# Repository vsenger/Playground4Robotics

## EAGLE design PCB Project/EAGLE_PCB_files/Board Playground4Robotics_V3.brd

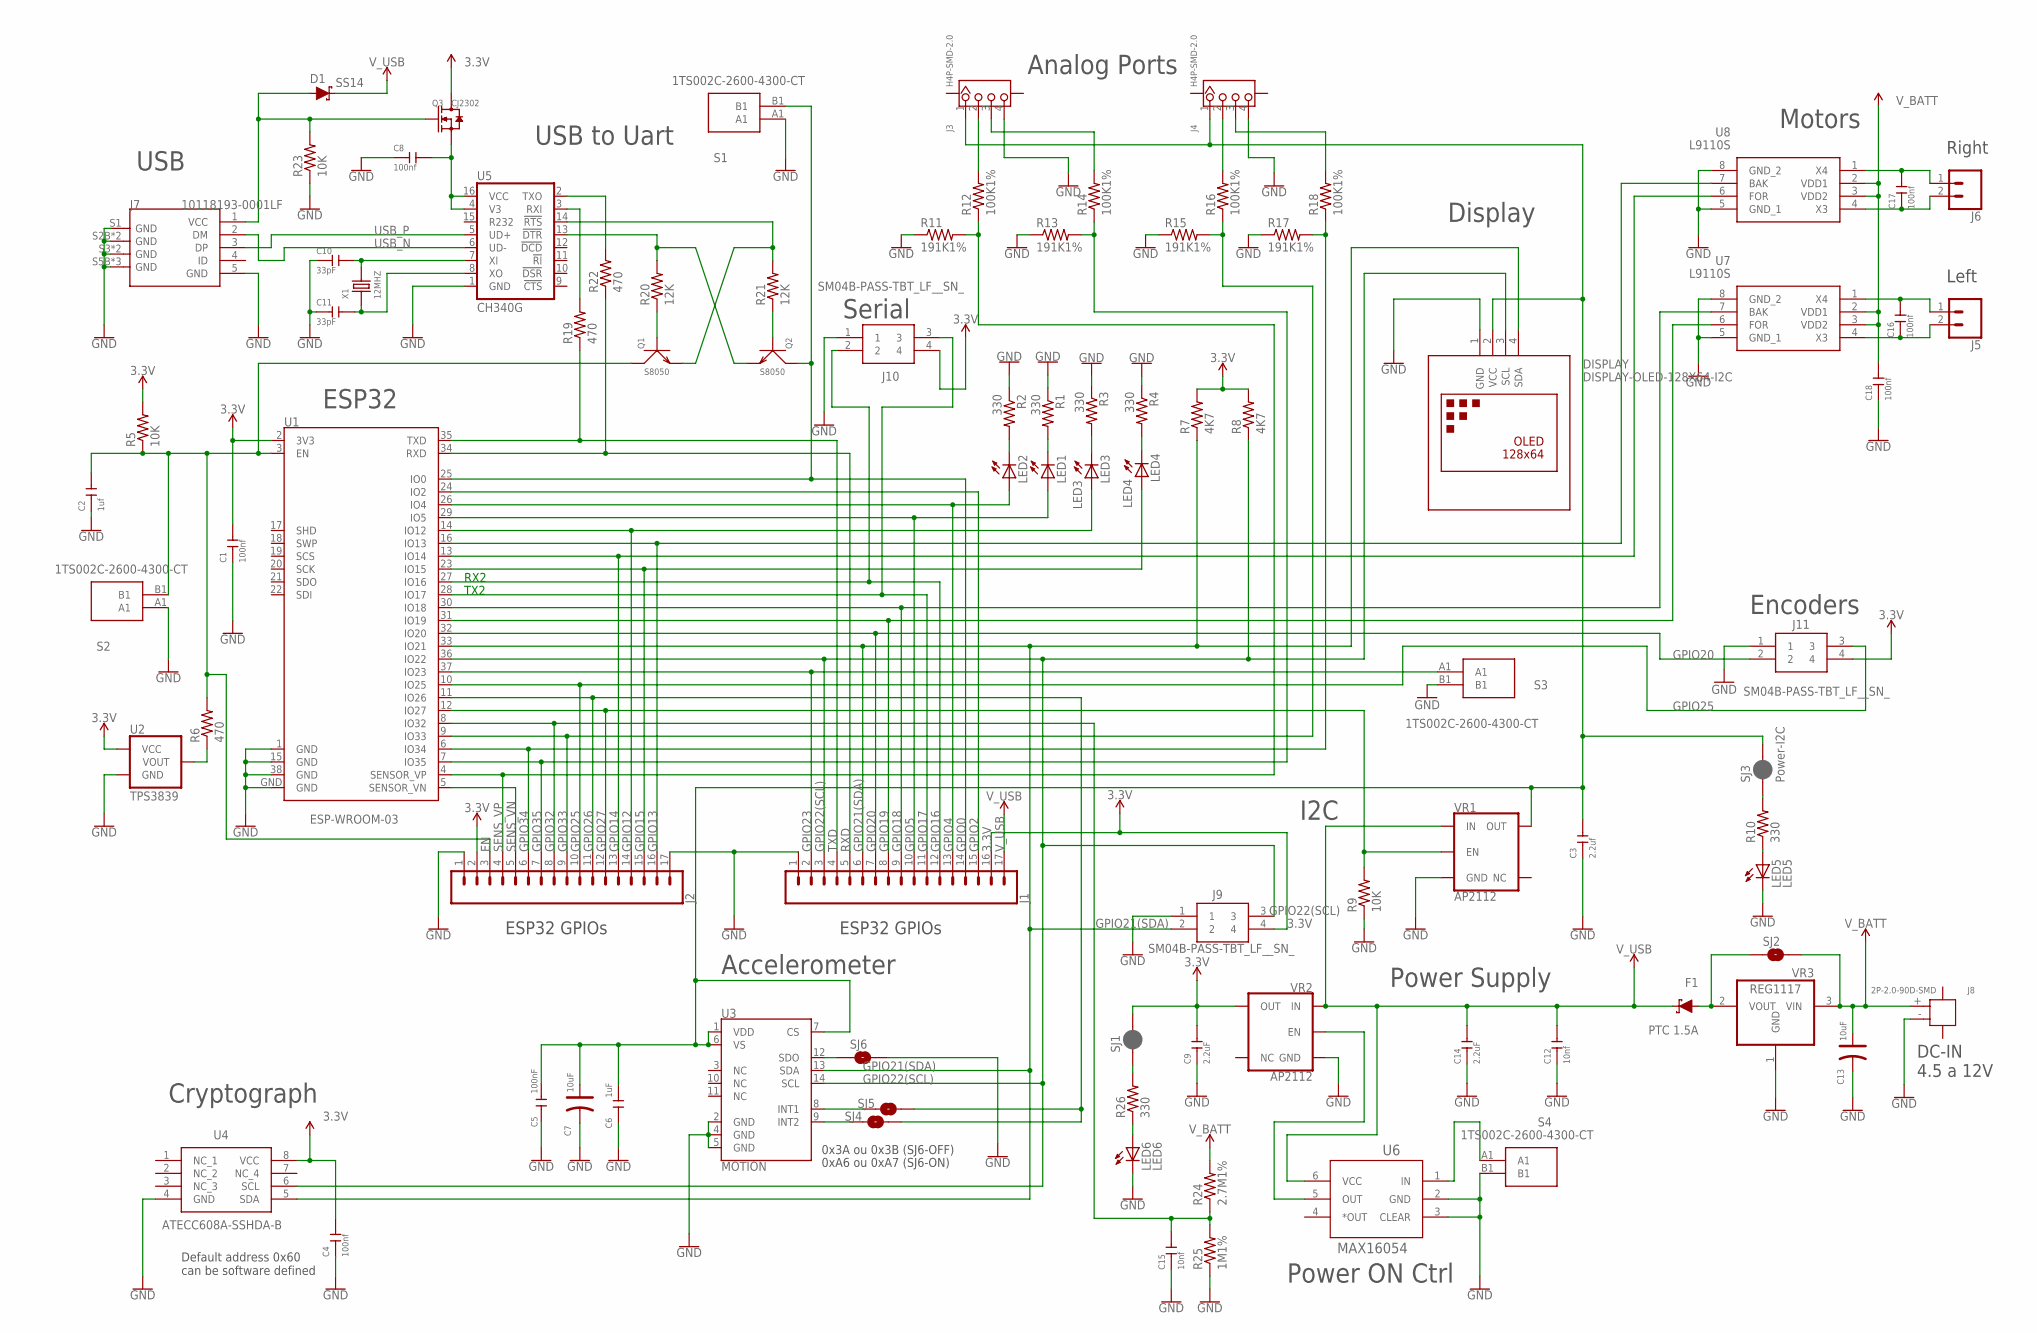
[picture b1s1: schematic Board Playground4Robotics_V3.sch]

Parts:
C1, C4, C8, C16, C17, C18: 100nf; C0603
C2: 1uf; C0603
C3: 2.2uf; C0603
C5: 100nF; C0603
C6: 1uF; C0805
C7, C13: 10uF; AVX-A
C9, C14: 2.2uF; C0603
C10, C11: 33pF; C0603
C12, C15: 10nf; C0603
D1: SS14; SMA-DIODE
DISPLAY: DISPLAY-OLED-128X64-I2C
F1: PTC 1.5A; SMA-DIODE
J1, J2: CONN_17; 1X17
J3, J4: H4P-SMD-2.0; HW4-SMD-2.0
J5, J6: CONN_02POLAR; MOLEX-1X2
J7: 10118193-0001LF; MICRO-USB5+6P-SMD-0.65-B
J8: 2P-2.0-90D-SMD; HW2-SMD-2.0-90D
J9, J10, J11: SM04B-PASS-TBT_LF__SN_; SM04B-PASS-TBT
LED1: LED1; LED-0603
LED2: LED2; LED-0603
LED3: LED3; LED-0603
LED4: LED4; LED-0603
LED5: LED5; LED-0603
LED6: LED6; LED-0603
Q1, Q2: S8050; SOT-23
Q3: CJ2302; SOT-23
R1, R2, R3, R4, R10, R26: 330; 0805
R5, R9, R23: 10K; 0805
R6, R19, R22: 470; 0805
R7, R8: 4K7; 0805
R11, R13, R15, R17: 191K1%; 0805
R12, R14, R16, R18: 100K1%; 0805
R20, R21: 12K; 0805
R24: 2.7M1%; 0805
R25: 1M1%; 0805
S1, S2, S3, S4: 1TS002C-2600-4300-CT; 1TS002C26004300CT
SJ1: Power-Led; SMT-JUMPER_2_NC_PASTE_SILK
SJ2, SJ6: ADXL_ADDRESS; SJ_2S-NO
SJ3: Power-I2C; SMT-JUMPER_2_NC_PASTE_SILK
SJ4, SJ5: INT1; SJ_2S-NO
U1: ESP-WROOM-03
U2: TPS3839; SOT23-3
U3: MOTION; LGA-14
U4: ATECC608A-SSHDA-B; SOIC127P600X175-8N
U5: CH340G; SO016
U6: MAX16054; SOT23-6
U7, U8: L9110S; SOIC127P600X175-8N
VR1, VR2: AP2112; SOT23-5
VR3: REG1117; SOT223
X1: 12MHZ; X2-SMD-5.0X3.2X1.3MM

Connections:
3.3V: C1.2, C4.2, C9.2, J1.16, J2.2, J9.4, J10.4, J11.4, Q3.3 (D), R5.2, R7.2, R8.2, SJ1.2, U1.2 (3V3), U2.3 (VCC), U4.8 (VCC), VR2.5 (OUT)
EN: C2.2, J2.3, Q1.3 (C), R5.1, R6.2, S2.B1, U1.3 (EN)
GND: C1.1, C2.1, C3.1, C4.1, C5.1, C6.2, C7.-, C8.1, C9.1, C10.1, C11.1, C12.1, C13.-, C14.1, C15.1, C18.1, DISPLAY.1 (GND), J1.1, J2.1, J2.17, J3.4, J4.4, J7.5 (GND), J7.S1 (GND), J7.S2B (GND), J7.S2T (GND), J7.S3 (GND), J7.S4 (GND), J7.S5B (GND), J7.S5T (GND), J7.S6 (GND), J8.- (2), J9.1, J10.1, J11.1, LED5.C, LED6.C, R1.1, R2.1, R3.1, R4.1, R9.1, R11.1, R13.1, R15.1, R17.1, R23.1, R25.1, S1.A1, S2.A1, S3.B1, S4.B1, SJ6.2, U1.1 (GND), U1.15 (GND), U1.38 (GND), U1.GND, U2.1 (GND), U3.2 (GND), U3.4 (GND), U3.5 (GND), U4.4 (GND), U5.1 (GND), U6.2 (GND), U6.3 (CLEAR), U7.5 (GND_1), U7.8 (GND_2), U8.5 (GND_1), U8.8 (GND_2), VR1.2 (GND), VR2.2 (GND), VR3.1 (GND)
GPIO0: J1.14, Q2.3 (C), S1.B1, U1.25 (IO0)
GPIO2: J1.15, U1.24 (IO2)
GPIO4: J1.13, LED2.A, U1.26 (IO4)
GPIO5: J1.10, LED1.A, U1.29 (IO5)
GPIO12: J2.14, LED3.A, U1.14 (IO12)
GPIO13: J2.16, U1.16 (IO13), U8.7 (BAK)
GPIO14: J2.13, U1.13 (IO14), U8.6 (FOR)
GPIO15: J2.15, LED4.A, U1.23 (IO15)
GPIO16: J1.12, J10.2, U1.27 (IO16)
GPIO17: J1.11, J10.3, U1.28 (IO17)
GPIO18: J1.9, U1.30 (IO18), U7.7 (BAK)
GPIO19: J1.8, U1.31 (IO19), U7.6 (FOR)
GPIO20: J1.7, J11.2, U1.32 (IO20)
GPIO21(SDA): DISPLAY.4 (SDA), J1.6, J9.2, R7.1, U1.33 (IO21), U3.13 (SDA), U4.5 (SDA)
GPIO22(SCL): DISPLAY.3 (SCL), J1.3, J9.3, R8.1, U1.36 (IO22), U3.14 (SCL), U4.6 (SCL)
GPIO23: J1.2, S3.A1, U1.37 (IO23)
GPIO25: J2.10, J11.3, U1.10 (IO25)
GPIO26: J2.11, SJ4.2, SJ5.2, U1.11 (IO26)
GPIO27: J2.12, R9.2, U1.12 (IO27), VR1.3 (EN)
GPIO32: C15.2, J2.8, R24.1, R25.2, U1.8 (IO32)
GPIO33: J2.9, R15.2, R16.1, U1.9 (IO33)
GPIO34: J2.6, R17.2, R18.1, U1.6 (IO34)
GPIO35: J2.7, R13.2, R14.1, U1.7 (IO35)
unnamed: D1.A, J7.1 (VCC), Q3.1 (G), R23.2
unnamed: C17.2, J6.1, U8.1 (X4)
unnamed: R6.1, U2.2 (VOUT)
unnamed: J3.2, R12.2
unnamed: SJ5.1, U3.8 (INT1)
unnamed: SJ4.1, U3.9 (INT2)
unnamed: C8.2, Q3.2 (S), U5.4 (V3), U5.16 (VCC)
unnamed: S4.A1, U6.1 (IN)
unnamed: C10.2, U5.7 (XI), X1.2
unnamed: U6.5 (OUT), VR2.3 (EN)
unnamed: Q1.1 (B), R20.1
unnamed: C11.2, U5.8 (XO), X1.1
unnamed: SJ6.1, U3.12 (SDO)
unnamed: C17.1, J6.2, U8.4 (X3)
unnamed: C16.2, J5.1, U7.1 (X4)
unnamed: C16.1, J5.2, U7.4 (X3)
unnamed: J3.3, R14.2
unnamed: Q2.1 (B), R21.1
unnamed: F1.A, SJ2.1, VR3.2 (VOUT)
unnamed: LED2.C, R2.2
unnamed: LED1.C, R1.2
unnamed: Q1.2 (E), R21.2, U5.14 (!RTS)
unnamed: LED4.C, R4.2
unnamed: LED3.C, R3.2
unnamed: Q2.2 (E), R20.2, U5.13 (!DTR)
unnamed: J4.2, R16.2
unnamed: J4.3, R18.2
unnamed: C3.2, C5.2, C6.1, C7.+, DISPLAY.2 (VCC), J3.1, J4.1, SJ3.2, U3.1 (VDD), U3.6 (VS), U3.7 (CS), VR1.5 (OUT)
unnamed: R19.2, U5.3 (RXI)
unnamed: R22.2, U5.2 (TXO)
unnamed: LED6.A, R26.1
unnamed: R26.2, SJ1.1
unnamed: LED5.A, R10.1
unnamed: R10.2, SJ3.1
RXD: J1.5, R22.1, U1.34 (RXD)
SENS_VN: J2.5, U1.5 (SENSOR_VN)
SENS_VP: J2.4, R11.2, R12.1, U1.4 (SENSOR_VP)
TXD: J1.4, R19.1, U1.35 (TXD)
USB_N: J7.2 (DM), U5.6 (UD-)
USB_P: J7.3 (DP), U5.5 (UD+)
V_BATT: C13.+, C18.2, J8.+ (1), R24.2, SJ2.2, U7.2 (VDD1), U7.3 (VDD2), U8.2 (VDD1), U8.3 (VDD2), VR3.3 (VIN)
V_USB: C12.2, C14.2, D1.C, F1.C, J1.17, U6.6 (VCC), VR1.1 (IN), VR2.1 (IN)

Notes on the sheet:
USB
I2C
Accelerometer
Default address 0x60 can be software defined
Serial
ESP32
Power Supply
USB to Uart
Analog Ports
ESP32 GPIOs
RX2
TX2
Display
0x3A ou 0x3B (SJ6-OFF)
0xA6 ou 0xA7 (SJ6-ON)
Power ON Ctrl
Cryptograph
Encoders
Motors
Left
Right
DC-IN 4.5 a 12V

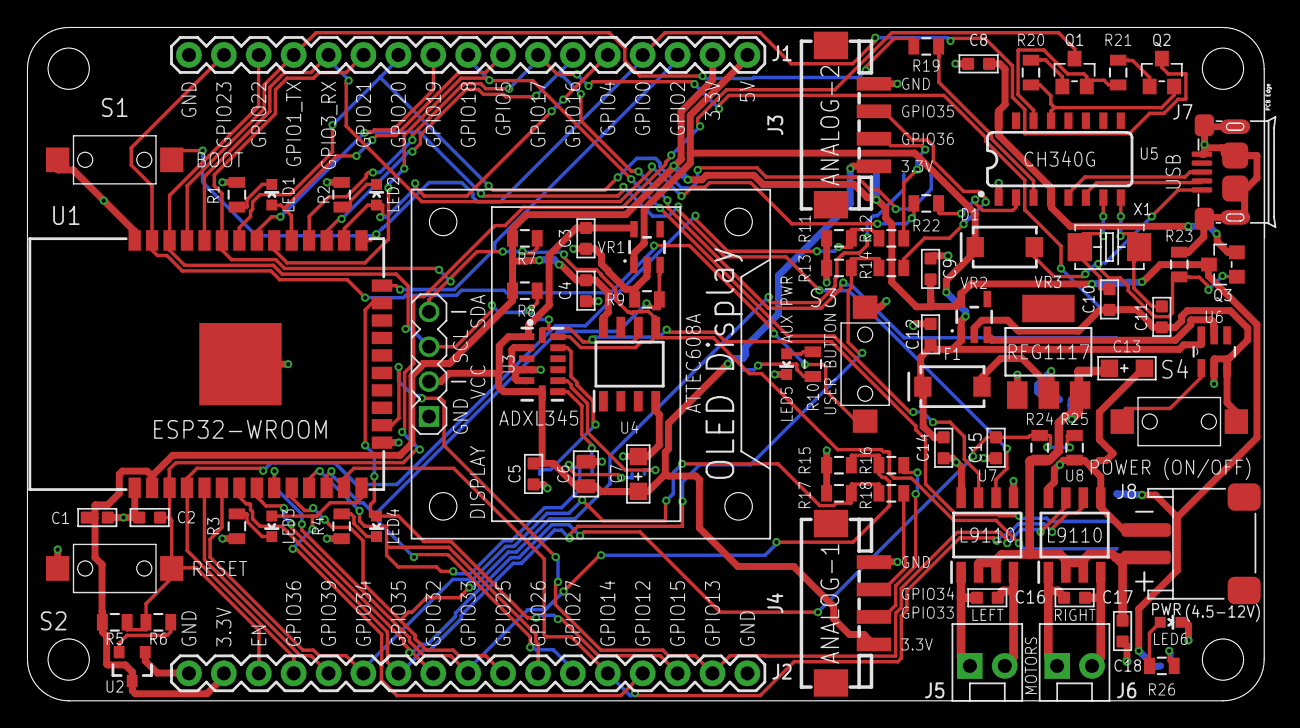
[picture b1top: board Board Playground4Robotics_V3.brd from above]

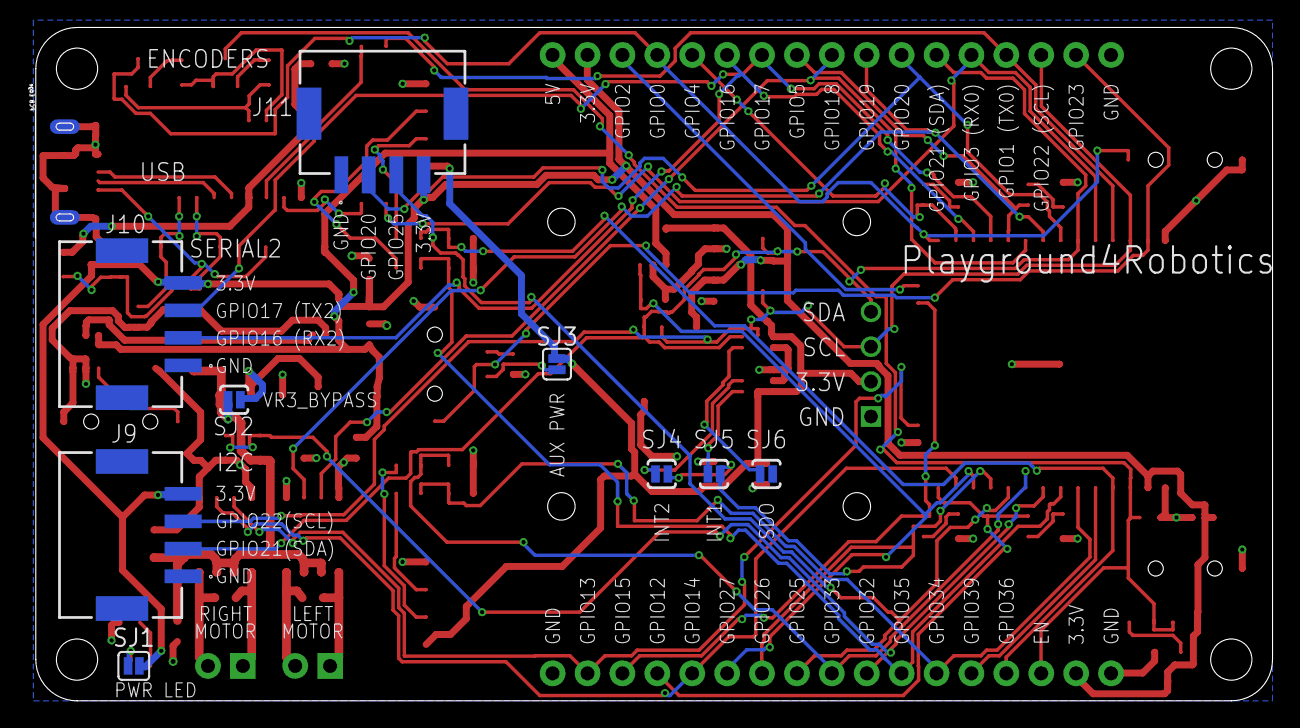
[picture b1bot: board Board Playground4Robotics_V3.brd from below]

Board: 2 copper layers, 90.0 x 49.0 mm, 89 parts (9 on the bottom side), 68 nets.

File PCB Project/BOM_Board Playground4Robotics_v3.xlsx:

Qty | Value | Package | Parts | Description | PART_NUMBER | Unit PRICE (100 PCBs) | SUBTOTAL
6 | 330 | 0805 | R1, R2, R3, R4, R10, R26 | 330 ±1% 1/8W ±100ppm/℃ 0805 Chip Resistor - Surface Mount RoHS | RC0805FR-07330RL | 9.9819999999999996E-3 | 5.9892000000000001E-2
3 | 10K | 0805 | R5, R9, R23 | 10K ±5% 1/8W ±200ppm/℃ 0805 Chip Resistor - Surface Mount RoHS | CR0805J80103G | 2.5929999999999998E-3 | 7.7789999999999995E-3
3 | 470 | 0805 | R6, R19, R22 | 470 ±1% 1/8W ±100ppm/℃ 0805 Chip Resistor - Surface Mount RoHS | RC0805FR-07470RL | 2.8029999999999999E-3 | 8.4089999999999998E-3
2 | 4K7 | 0805 | R7, R8 | 4.7K ±1% 1/8W ±100ppm/℃ 0805 Chip Resistor - Surface Mount RoHS | RCT054K7 FLF | 7.9220000000000002E-3 | 1.5844E-2
4 | 191K1% | 0805 | R11, R13, R15, R17 | 191K ±1% 1/8W ±100ppm/℃ 0805 Chip Resistor - Surface Mount RoHS | AC0805FR-07191KL | 5.4120000000000001E-3 | 2.1648000000000001E-2
4 | 100K1% | 0805 | R12, R16, R14, R18 | 100K ±1% 1/8W ±100ppm/℃ 0805 Chip Resistor - Surface Mount RoHS | RS-05K1003FT | 7.0280000000000004E-3 | 2.8112000000000002E-2
2 | 12K | 0805 | R20, R21 | 12K ±5% 1/8W ±100ppm/℃ 0805 Chip Resistor - Surface Mount RoHS | AC0805FR-0712KL | 1.853E-3 | 3.7060000000000001E-3
1 | 2.7M1% | 0805 | R24 | 2.7M ±1% 1/8W ±100ppm/℃ 0805 Chip Resistor - Surface Mount RoHS | 0805W8F2704T5E | 1.825E-3 | 1.825E-3
1 | 1M1% | 0805 | R25 | 1M ±1% 1/8W ±100ppm/℃ 0805 Chip Resistor - Surface Mount RoHS | RC0805FR-071ML | 4.1520000000000003E-3 | 4.1520000000000003E-3
7 | 100nf | C0603 | C1, C4, C5, C8, C16, C17, C18 | 100nF ±10% 50V X7R 0603 Multilayer Ceramic Capacitors MLCC - SMD/SMT RoHS | C0603B104K500NT | 7.8560000000000001E-3 | 5.4991999999999999E-2
1 | 1uF | C0603 | C2 | 1uF ±10% 16V X7R 0603Multilayer Ceramic Capacitors MLCC - SMD/SMT RoHS | CL10A105KO8NNNC | 6.6E-3 | 6.6E-3
3 | 2.2uf | C0603 | C3, C9, C14 | 2.2uF ±10% 16V X5R 0603 Multilayer Ceramic Capacitors MLCC - SMD/SMT RoHS | 0603X225K160NT | 1.7375999999999999E-2 | 5.2127999999999994E-2
1 | 1uF | C0805 | C6 | 1uF ±10% 16V X7R 0805 Multilayer Ceramic Capacitors MLCC - SMD/SMT RoHS | FS21B105K160ECG | 3.7949999999999998E-2 | 3.7949999999999998E-2
2 | 10uF | AVX-A | C7, C13 | 10uF ±10% 10V 3 Ω @ 100kHz -55℃ ~ +125℃ CASE-A_3216 Tantalum Capacitors RoHS | CA45-A-16V-10uF-K | 6.7254999999999995E-2 | 0.13450999999999999
2 | 33pF | C0603 | C10, C11 | 33pF ±5% 50V C0G 0603 Multilayer Ceramic Capacitors MLCC - SMD/SMT RoHS | 0603N330F500CT | 1.4840000000000001E-2 | 2.9680000000000002E-2
2 | 10nf | C0603 | C12, C15 | 10nF ±5% 50V NP0 0603 Multilayer Ceramic Capacitors MLCC - SMD/SMT RoHS | 0603B103J500CT | 7.1798000000000001E-2 | 0.143596
1 | 12MHZ | X2-SMD-5.0X3.2X1.3MM | X1 | 12MHz ±30ppm 20pF 150Ω SMD-5032_2P SMD Crystal Resonators RoHS | XSHEELNANF-12MHZ | 0.160606 | 0.160606
4 | green | LED-0603 | LED1, LED2, LED3, LED4 | Green 520~535nm 0603 Light Emitting Diodes (LED) RoHS | 19-217/GHC-YR1S2/3T | 3.5455E-2 | 0.14182
1 | yellow | LED-0603 | LED5 | Yellow 585.5~594.5nm 0603 Light Emitting Diodes (LED) RoHS | 19-217/Y5C-AP1Q2/3T | 2.0181000000000001E-3 | 2.0181000000000001E-3
1 | red | LED-0603 | LED6 | Red 617.5~633.5nm 0603 Light Emitting Diodes (LED) RoHS | 19-217/R6C-AL1M2VY/3T | 1.7727E-2 | 1.7727E-2
1 | SS14 | SMA-DIODE | D1 | SMA Schottky Barrier Diodes (SBD) RoHS | SS14 | 9.6050000000000007E-3 | 9.6050000000000007E-3
1 | FUSE PTC 1.5 A | 1206 | D2 / F1 | Polymeric 8V 1.5A 200ms 290mΩ 1206 PTC Resettable | 1206L075THYR | 3.4000000000000002E-2 | 3.4000000000000002E-2
2 | AP2112 | SOT23-5 | VR1, VR2 | AP2112-3.3v Fixed 6V 3.3V 600mA SOT-25 Low Dropout Regulators(LDO) RoHS | AP2112K-3.3TRG1 | 0.124252 | 0.248504
1 | REG1117 5volts | SOT223 | VR3 | 800mA and 1A Low Dropout (LDO) Positive Regulator 5 volts | AMS1117-5.0 | 3.7600000000000001E-2 | 3.7600000000000001E-2
1 | ESP-WROOM-03 | ESP-WROOM-03 | U1 | ESP32 Module WIFI Modules RoHS | ESP32-WROOM-32 | 2.6151520000000001 | 2.6151520000000001
1 | TPS3839 | SOT23-3 | U2 | Simple reset/Power-on reset 1 Push-pull,Totem pole Low effective 2.93V SOT-23(S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 | TPS3839K33DBZR | 0.39696999999999999 | 0.39696999999999999
1 | MOTION | LGA-14 | U3 | Analog Devices ADXL345 3-Axis SPI/I2C 2/4/8/16g Accelerometer | ADXL345BCCZ-RL7 | 1.1636359999999999 | 1.1636359999999999
1 | ATECC608A-SSHDA-B | SOIC127P600X175-8N | U4 | Cryptoathentication ECC608A SOIC | ATECC608A_SSHDA-B | 1.827 | 1.827
1 | CH340G | SO016 | U5 | Transceiver USB 2.0 2Mbps SOP-16_150mil USB ICs RoHS | CH340G | 0.275758 | 0.275758
1 | MAX16054 | SOT23-6 | U6 | TSOT-23-6 Interface - Specialized RoHS | MAX16054AZT+T | 1.204545 | 1.204545
2 | L9110S | SOIC127P600X175-8N | U7, U8 | Motor Drivers SOP-8_150mil RoHS | L9110S | 0.11459999999999999 | 0.22919999999999999
2 | S8050 | SOT-23 | Q1, Q2 | NPN 500mA 25V 300mW SOT-23 Transistors (NPN/PNP) RoHS | S8050 | 7.5909999999999997E-3 | 1.5181999999999999E-2
1 | CJ2302 | SOT-23 | Q3 | N Channel 20V 2.1A 1.2V @ 50uA 60 mΩ @ 3.6A,4.5V 350mW SOT-23(SOT-23-3) MOSFET 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 | CJ2302 S2 | 3.0800000000000001E-2 | 3.0800000000000001E-2
4 | CONN_17 | 1X17 | J1, J2 | 10P 2.54MM Stackable Long Connector Female Pin Header (Arduino style) | SeeedStudio (320030001) |  | 0
2 | H4P-SMD-2.0 | HW4-SMD-2.0 | J3, J4 | PA SMD Wire To Board / Wire To Wire Connector RoHS | BM04B-PASS-TFT(LF)(SN) | 0.32150000000000001 | 0.64300000000000002
2 | KK | MOLEX-1X2 | J5, J6 | Header Male Pin 0.100"(2.54mm) 2 Through Hole,P=2.54mm Wire To Board / Wire To 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 | A2543WV-2P | 2.63E-2 | 5.2600000000000001E-2
1 | 10118193-0001LF | MICRO-USB5+6P-SMD-0.65-B | J7 | MICRO-USB-SMD-B-(10118193-0001LF) | (10118193-0001LF) ou (U254-051T-4BH83-F1S) | 0.14419999999999999 | 0.14419999999999999
1 | 2P-2.0-90D-SMD | HW2-SMD-2.0-90D | J8 | CONN-HEADER-SMD-PH-SIDE-(2P-2.0MM) | S2B-PH-SM4-TB(LF)(SN) | 0.12670000000000001 | 0.12670000000000001
3 | SM04B-PASS-TBT_LF__SN_ | SM04B-PASS-TBT | J9, J10, J11 | PA Header Male Pin 0.079"(2.00mm) 4 Through Hole,P=2mm Wire To Board / Wire To 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 | SM04B-PASS-TBT(LF)(SN) | 0.36818200000000001 | 1.104546
4 | 1TS002C-2600-4300-CT | 1TS002C26004300CT | S1, S2, S3, S4 | SPST 50mA @ 12VDC Top Actuated Rectangular Button SMD,6x3.5x4.3mm Tactile Switc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 | 1TS002C-2400-4300-CT | 2.9360000000000001E-2 | 0.11744
1 | DISPLAY-OLED-128X64-I2C | DISPLAY-OLED-128X64-I2C | DISPLAY | 128x64 Dot Matrix OLED Module based on SSD1306 chip | 128x64 oled | 2.1 | 2.1
 | CABLES components
5 | conectors Housing (ANALOG) |  | J3 e J4 (analogs) / J9, J10 e J11 (I2C, Serial and Encoders) | PA 4 0.079"(2.00mm) 1 Male Housing,P=2mm Rectangular Connectors Housings RoHS | PAP-04V-S | 4.65E-2 | 0.23249999999999998
2 | conectors Housing (MOTORS) |  | J5 e J6 (motors) | 2 0.100"(2.54mm) 1 P=2.54mm Rectangular Connectors Housings RoHS | A2543H-2P | 1.38E-2 | 2.76E-2
1 | conectors Housing (DC-IN) |  | J8 (DC_IN) | PA 2 0.079"(2.00mm) 1 Male Housing,P=2mm Rectangular Connectors Housings RoHS | PAP-02V-S | 3.85E-2 | 3.85E-2
22 | Crimping terminals (ANALOG and DC-IN) |  | J3,J4,J8,J9,J10,J11 (terminals) | Crimping terminal 24~28 0.08~0.21 UL , RoHS , CSA Terminals RoHS | SPHD-002T-P0.5 | 1.17E-2 | 0.25740000000000002
4 | Crimping terminals (MOTORS) |  | J5, J6 (terminals) | Crimping terminal 22~28 RoHS , REACH Terminals RoHS | A2543-TB | 1.06E-2 | 4.24E-2
 |  |  |  |  |  | Total | 13.9078321

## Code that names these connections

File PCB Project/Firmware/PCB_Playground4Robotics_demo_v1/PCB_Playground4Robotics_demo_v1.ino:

//Upload Instructions
//  Tools
//  Board: Node32s
//  UploadSpeed: 230400
//  FlashFrequency: 80MHz



/****** ESP32 GPIO MAP ******  

GPIO0 -> Firmware Upload Mode
GPIO1 -> TXD
GPIO3 -> RXD

GPIO5 -> Led 1
GPIO4 -> Led 2
GPIO12 -> Led 3
GPIO15 -> Led 4

GPIO16 -> Serial 2 (RX)
GPIO17 -> Serial 2 (TX)

GPIO21 -> I2C (SDA)
GPIO22 -> I2C (SCL)

GPIO23 -> User Button (0=pressed / 1=not pressed)

GPIO26 -> ADXL345 sensor Interrupt Input (optional- must be configured conecting SJ4 or SJ5)

GPIO27 -> Sensors and Display Power control (0=Power OFF / 1=Power ON)

GPIO32 -> Battery voltage (Analog INPUT)
GPIO33   -> (External Analog INPUT)
GPIO34   -> (External Analog INPUT)
GPIO35   -> (External Analog INPUT)  
GPIO36 SENSORVP -> (External Analog INPUT) 

GPIO18 -> RIGHT MOTOR - BAK
GPIO19 -> RIGHT MOTOR - FOR

GPIO13 -> LEFT MOTOR - BAK
GPIO14 -> LEFT MOTOR - FOR

GPIO20 -> ENCODER
GPIO25 -> ENCODER

GPIO6 a GPIO11 -> Do not Use (Flash Memory)

GPIO2 -> External GPIO
GPIO4 -> External GPIO
GPIO5 ->  External GPIO
GPI12 ->  External GPIO
GPI15 ->  External GPIO
GPI12 ->  External GPIO
SensorVN - >  External GPIO

*/

#include <WiFi.h>
#include <ESPmDNS.h>
#include <WiFiUdp.h>
#include <ArduinoOTA.h>
#include <Wire.h>
#include "ssd1306.h"
#include <Adafruit_Sensor.h>
#include <Adafruit_ADXL345_U.h>

// Include logo images
#include "Logo_AWS.h"

#include <SparkFun_ATECCX08a_Arduino_Library.h> //Click here to get the library: http://librarymanager/All#SparkFun_ATECCX08a
//#include <Wire.h>

ATECCX08A atecc;


#define hostName "PCB_PlayGround4Robotics_1"

/* Assign a unique ID to this sensor at the same time */
Adafruit_ADXL345_Unified accel = Adafruit_ADXL345_Unified(12345);

#define SSD1306_128_64

long startTime;

#define led1 5
#define led2 4
#define led3 12
#define led4 15
#define delayLeds 100
bool direcao = false;
int userButtonState = 1;


// Motor A (Right)
int motor1_IA = 13; 
int motor1_IB = 14; 

// Motor B (Left)
int motor2_IA = 18; 
int motor2_IB = 19; 

double AN_36_voltage;
double AN_35_voltage;
double AN_34_voltage;
double AN_33_voltage;

double batteryVoltage;
bool batteryChargeStatus ;  //(1-CHARGED)
int batteryStatusPerCent;

#define batteryStatusPin 25

float Xacc;
float Yacc;
float Zacc;

const char* ssid = "ASSIST";
const char* password = "Assist@2017";

#define SSD1306_128_32

void setup() {
  pinMode(27,OUTPUT);       //power ON sensors and OLED display
  digitalWrite(27,HIGH);
  pinMode(25,INPUT);        
  pinMode(23,INPUT_PULLUP);    //enable user button pull-up
  delay(2000);

  Serial.begin(115200);
  Serial2.begin(115200);

  //checkAttec608();
  
  // sets the pins as outputs:
  pinMode(led1,OUTPUT);
  pinMode(led2,OUTPUT);
  pinMode(led3,OUTPUT);
  pinMode(led4,OUTPUT);
  pinMode(motor1_IA, OUTPUT);
  pinMode(motor1_IB, OUTPUT);
  pinMode(motor2_IA, OUTPUT);
  pinMode(motor2_IB, OUTPUT);
  digitalWrite(motor1_IA,LOW);
  digitalWrite(motor1_IB,LOW);
  digitalWrite(motor2_IA,LOW);
  digitalWrite(motor2_IB,LOW);
  digitalWrite(led1,LOW);
  digitalWrite(led2,LOW);
  digitalWrite(led3,LOW);
  digitalWrite(led4,LOW);


  Wire.begin();  
  ssd1306_128x64_i2c_init();                     // Initialze SSD1306 OLED display
  ssd1306_clearScreen( );
  ssd1306_drawBitmap(0, 0, 128, 64, Logo_AWS);
  delay(3000);

  ssd1306_clearScreen( );
  ssd1306_setFixedFont(ssd1306xled_font5x7);            // Set font type (default 6x8)
  //oled.setTextXY(0,0);              // Set cursor position, start of line 0


  inicializaAcelerometro();

  Serial.println("Booting");
  Serial2.print("Ready...");
  WiFi.mode(WIFI_STA);
  WiFi.begin(ssid, password);
  while (WiFi.waitForConnectResult() != WL_CONNECTED) {
    Serial.println("Connection Failed! Rebooting...");
    delay(5000);
    ESP.restart();
  }

  inicializa_OTA();

  Serial.println("Ready");
  Serial.print("IP address: ");
  Serial.println(WiFi.localIP());
  IPoled();

  motor_left_Forward();
  delay(2000);
  motor_left_Stop();
  delay(2000);
  motor_left_Backwards();
  delay(2000);
  motor_left_Stop();
  delay(2000);
  motor_right_Forward();
  delay(2000);
  motor_right_Stop();
  delay(2000);
  motor_right_Backwards();
  delay(2000);
  motor_right_Stop();
  delay(2000);
  motor_left_Forward();
  motor_right_Forward();
  delay(2000);
  motor_left_Stop();
  motor_right_Stop();
  delay(2000);
  motor_left_Backwards();
  motor_right_Backwards();
  delay(2000);
  motor_left_Stop();
  motor_right_Stop();
  delay(2000);


  
}

void loop() {
  ArduinoOTA.handle();
  //testeLeds();
  delay(500);
  leAcelerometro();
  //le_voltagem_painelSolar();
  le_voltagem_bateria();
  le_battery_status();
  userButtonState = digitalRead(23);
  buttonOled();

  le_voltagem_portasAnalogicas();

  if (Serial2.available()>0){
    String serialText = "";
    while(Serial2.available()>0){
      serialText = serialText + char(Serial2.read()); 
    }
    serialtextToOled(serialText);
  }

}

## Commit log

2021-03-04 initial

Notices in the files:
parts and their libraries:
SparkFun-DiscreteSemi: Licensing: Creative Commons ShareAlike 4.0 International - https://creativecommons.org/licenses/by-sa/4.0
diy-modules: Released under the Creative Commons Attribution 4.0 International License: http://creativecommons.org/licenses/by/4.0
